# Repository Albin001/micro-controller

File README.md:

# micro-controller  
Micro controller used here is 8051
software: keil ,proteus

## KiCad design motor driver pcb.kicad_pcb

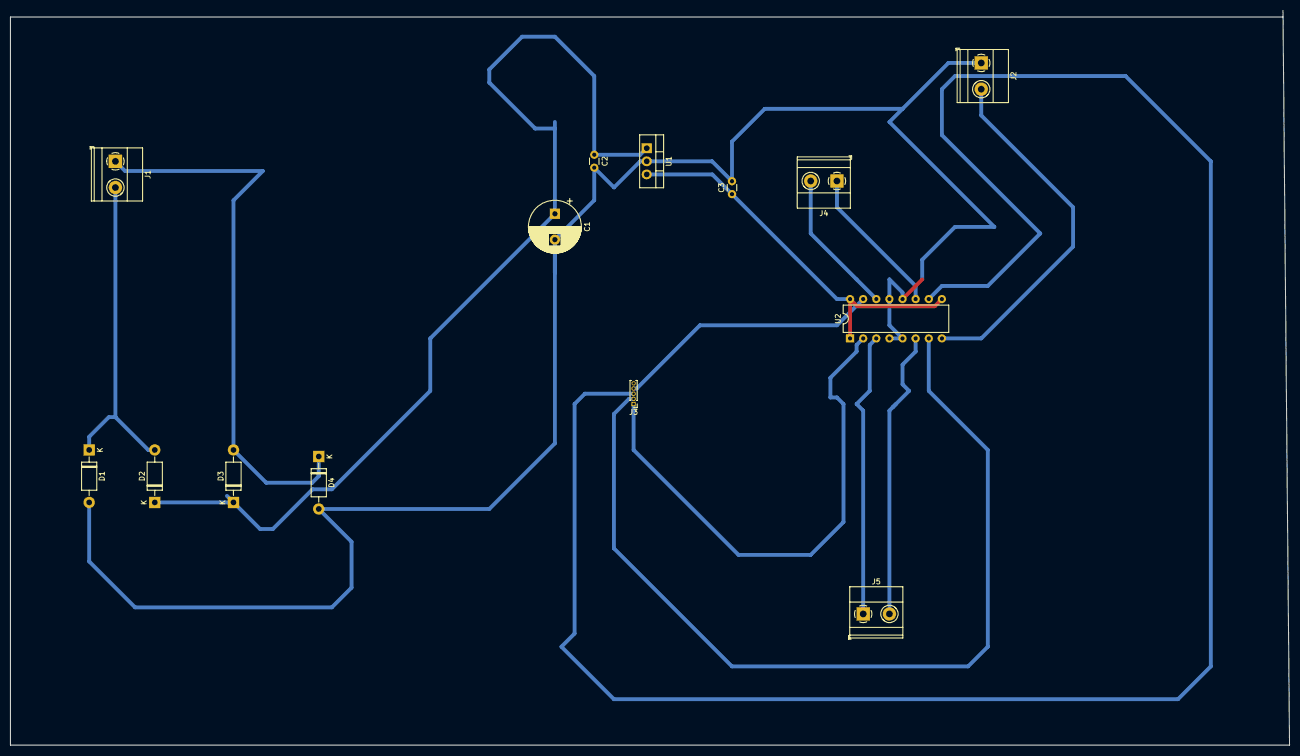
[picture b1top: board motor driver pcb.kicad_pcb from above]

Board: 2 copper layers, 247.6 x 142.2 mm, 14 parts (0 on the bottom side), 14 nets.

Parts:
C1: 1000uF; CP_Radial_D10.0mm_P5.00mm
C2, C3: 104; C_Disc_D3.0mm_W1.6mm_P2.50mm
D1, D2, D3, D4: 1N4007; D_DO-41_SOD81_P10.16mm_Horizontal
J1, J2, J4, J5: Screw_Terminal_01x02; TerminalBlock_Phoenix_MKDS-1,5-2-5.08_1x02_P5.08mm_Horizont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
J3: Screw_Terminal_01x05; PinHeader_1x05_P1.00mm_Vertical
U1: L7805; TO-220-3_Vertical
U2: L293D; DIP-16_W7.62mm

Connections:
GND: C1.2, C2.2, C3.2, D1.2, D4.2, J2.1, U1.2, U2.4, U2.5, U2.12, U2.13
unnamed: C1.1, C2.1, D2.1, D3.1, U1.1
unnamed: D1.1, D2.2, J1.2
unnamed: D3.2, D4.1, J1.1
in1: J3.1, U2.2
in2: J3.2, U2.7
in3: J3.3, U2.10
in4: J3.4, U2.15
out1: J5.1, U2.3
out2: J5.2, U2.6
out3: J4.1, U2.11
out4: J4.2, U2.14
vcc: C3.1, U1.3, U2.1, U2.9, U2.16
vcc1: J2.2, U2.8

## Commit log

2022-03-05 Lcd Interface file is added
2022-03-06 Motor Drive file is added
2022-03-06 External Interrupt file is added
2022-03-06 Keypad file is added
2022-03-06 Smart Irrigation File is Added
2022-03-07 one file is created
2022-03-07 Web page first version is added
2022-03-07 Home Automation C file is Added
2022-03-07 Smart Irrigation Version 1
2022-03-13 Irrigation project is Updated other sensor is added
2022-03-16 Motor Driver Intrerface Full is Complete
2022-03-20 seven segment file is added
2022-03-24 Keypad File using Pic18F4580 is ADDED
2022-03-24 Timer 1, Timer2 and Timer3 Program file using Pic18F4580 is added
2022-03-31 ADC using PIC18F4580 is added
2022-04-03 UltrasonicSensor sensor interface with 8051 is Added
2022-05-15 Counter using Interrupt in 8051 is Added
